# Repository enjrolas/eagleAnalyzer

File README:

Eagle Analyzer is a tool I built to learn more about what electronic
components hackers use in open-source electronic circuits.  There are
a couple files here.  Boards.py scrapes github for all .brd and
associated .sch files (.brd is the file format for circuit layout in
the popular circuit design software EagleCAD).  It's a little hacky (I
hardcoded how many pages are in the github search results), but it
pulls down all the eagle files.  

It's tricky to know if a file is an eagle file without looking inside
it.  .sch files are quite common in code, so just downloading all the
.sch files on github will give a lot of noise.  .brd files are less
common -- apart from eagle, it seems like the naming convention is
only used for some android code, and not very frequently.  To learn
the names of the components, though, we need the .sch files.  So, I
search for .brd files, download those files, and then check to see if
there's a .sch file with the same filepath.  If so, it's a good bet
that these are eagle files.

The next thing to do is to make a histogram to count the
frequency each component is used.  Histogram.py does exactly this.
Building the histogram itself is a bit tricky, because
people will give different names to the same components.  For example,
some people call a resistor 'R' and others call it 'RESISTOR'  -- it
depends on what library they use and whatever the naming convention
is.  So, some of this will require smart intervention, but to get
started, I use the ever-delightful beautifulSoup library to go through the .sch files and look for the <parts> tag,
Inside that tag are a bunch of <part> tags, each one listing the
unique parts in the circuit.  Each part has a 'deviceset' parameter
that's the closest thing to a unique name for a part that we're gonna
get, so I pull that parameter as the part name.  For each name, I
check a list of existing names that I've pulled to see if I've already
seen this name before.  If so, I add one to the number of times I've
seen this device.  If not, I add the device name to the list.

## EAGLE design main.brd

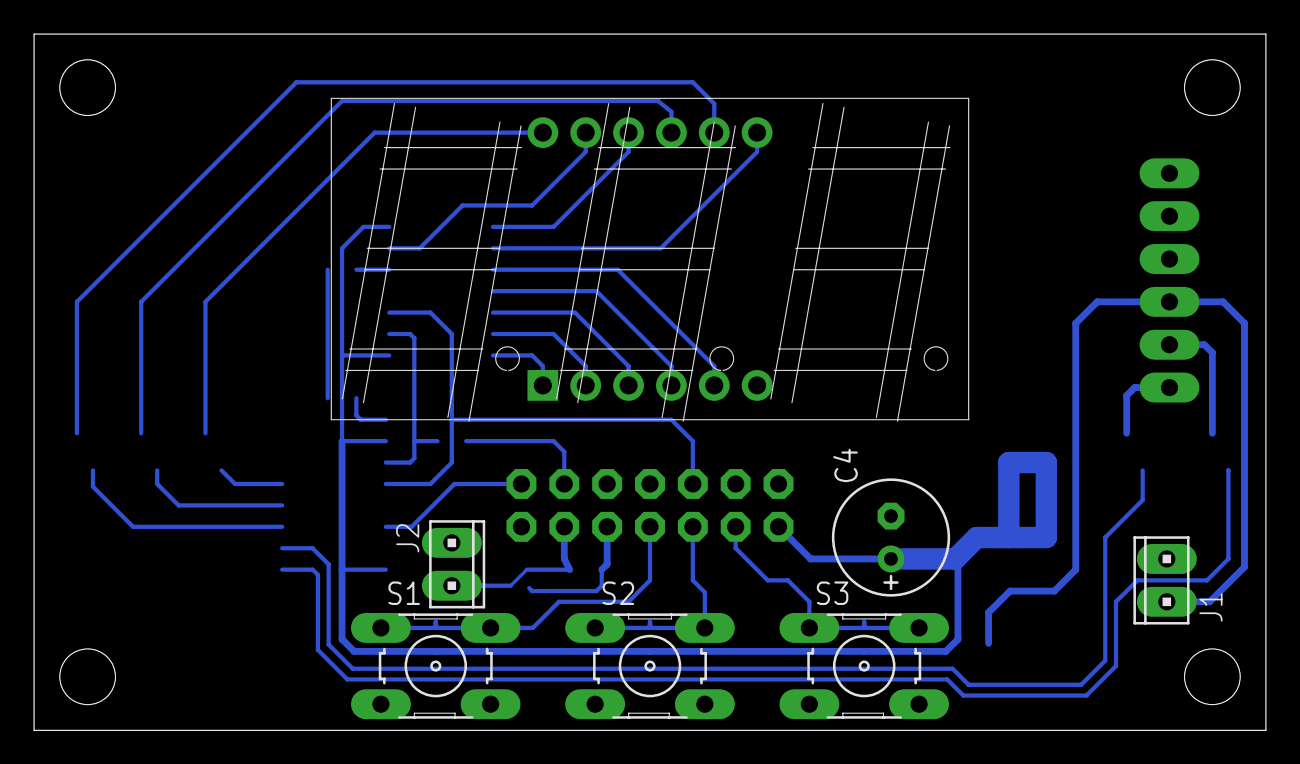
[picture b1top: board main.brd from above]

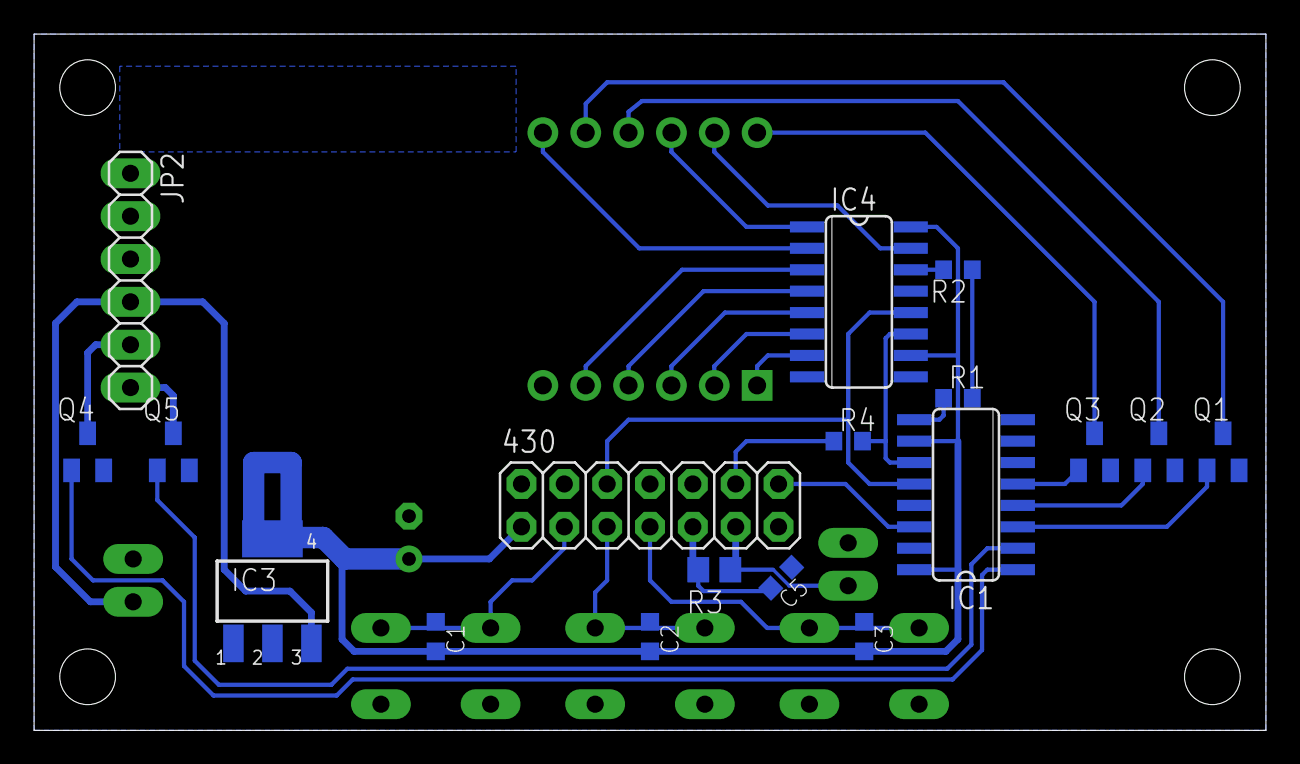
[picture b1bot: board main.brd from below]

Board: 2 copper layers, 73.0 x 41.3 mm, 25 parts (18 on the bottom side), 33 nets.

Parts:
430: 2X07
C1, C2, C3: C0603K
C4: E2,5-7
C5: 470nF; C0603K
IC1, IC4: 74LS595D; SO16
IC3: 317EMP; SOT223
J1, J2: 10X02MTA
JP2: 1X06
Q1, Q2, Q3, Q4, Q5: BSS123; SOT23
R1, R2, R4: 0; R0603
R3: 720ish; R0805
S1, S2, S3: B3F-10XX
U$1: BL-T52C-31; BL-T52X-31

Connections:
+5V: IC3.3, J1.2, JP2.4
GND: 430.2, 430.13, C4.-, C5.1, IC1.8, IC1.13, IC3.1, IC4.8, IC4.13, J1.1, J2.2, JP2.2, JP2.3, Q1.2, Q2.2, Q3.2, Q4.2, Q5.2, S1.3, S1.4, S2.3, S2.4, S3.3, S3.4
unnamed: IC4.15, U$1.P$8
unnamed: IC4.1, U$1.P$9
unnamed: IC4.7, U$1.P$1
unnamed: IC4.6, U$1.P$2
unnamed: IC4.5, U$1.P$3
unnamed: IC4.4, U$1.P$4
unnamed: IC4.3, U$1.P$5
unnamed: IC4.2, U$1.P$12
unnamed: Q1.3, U$1.P$11
unnamed: Q2.3, U$1.P$10
unnamed: Q3.3, U$1.P$7
unnamed: IC1.3, Q1.1
unnamed: 430.14, IC1.14
unnamed: IC4.14, R2.2
unnamed: 430.7, C3.1, S1.1, S1.2
unnamed: IC1.9, R1.1
unnamed: 430.11, J2.1, JP2.1, R3.1
unnamed: 430.3, C1.1, S3.1, S3.2
unnamed: R1.2, R2.1
unnamed: IC1.1, Q4.1
unnamed: IC1.11, IC4.11, R4.2
unnamed: IC1.4, Q2.1
unnamed: JP2.5, Q4.3
unnamed: IC1.5, Q3.1
unnamed: IC1.2, Q5.1
unnamed: 430.12, R4.1
unnamed: JP2.6, Q5.3
unnamed: 430.5, C2.1, S2.1, S2.2
unnamed: 430.6, IC1.12, IC4.12
unnamed: 430.9, C5.2, R3.2
VCC: 430.1, C1.2, C2.2, C3.2, C4.+, IC1.10, IC1.16, IC3.4, IC4.10, IC4.16

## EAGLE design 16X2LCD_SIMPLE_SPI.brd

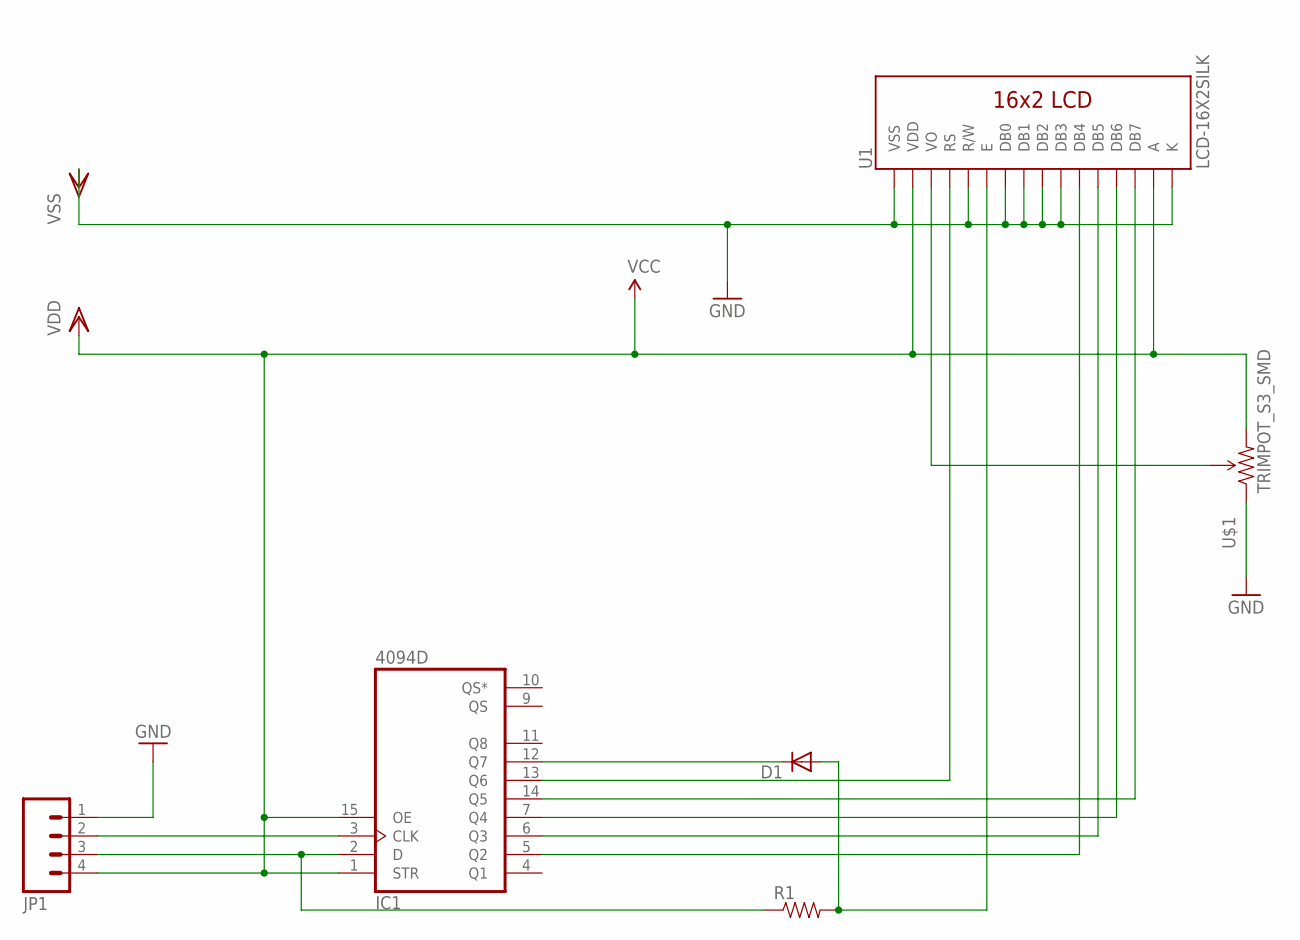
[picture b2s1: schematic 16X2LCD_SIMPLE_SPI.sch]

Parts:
D1: DIODESMA; SMA-DIODE
IC1: 4094D; SO16
JP1: M04PTH; 1X04
R1: RESISTOR1206; 1206
U1: LCD-16X2SILK; LCD-16X2
U$1: TRIMPOT_S3_SMD

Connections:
CLK: IC1.3 (CLK), JP1.2
DATA: IC1.2 (D), JP1.3, R1.1
GND: IC1.8 (VSS), JP1.1, U1.1 (VSS), U1.5 (R/W), U1.7 (DB0), U1.8 (DB1), U1.9 (DB2), U1.10 (DB3), U1.16 (K), U$1.P$1 (CCW)
unnamed: IC1.13 (Q6), U1.4 (RS)
unnamed: D1.A, R1.2, U1.6 (E)
unnamed: U1.3 (VO), U$1.P$2 (WIPER)
unnamed: D1.C, IC1.12 (Q7)
unnamed: IC1.5 (Q2), U1.11 (DB4)
unnamed: IC1.6 (Q3), U1.12 (DB5)
unnamed: IC1.7 (Q4), U1.13 (DB6)
unnamed: IC1.14 (Q5), U1.14 (DB7)
VDD: IC1.1 (STR), IC1.15 (OE), IC1.16 (VDD), JP1.4, U1.2 (VDD), U1.15 (A), U$1.P$3 (CW)

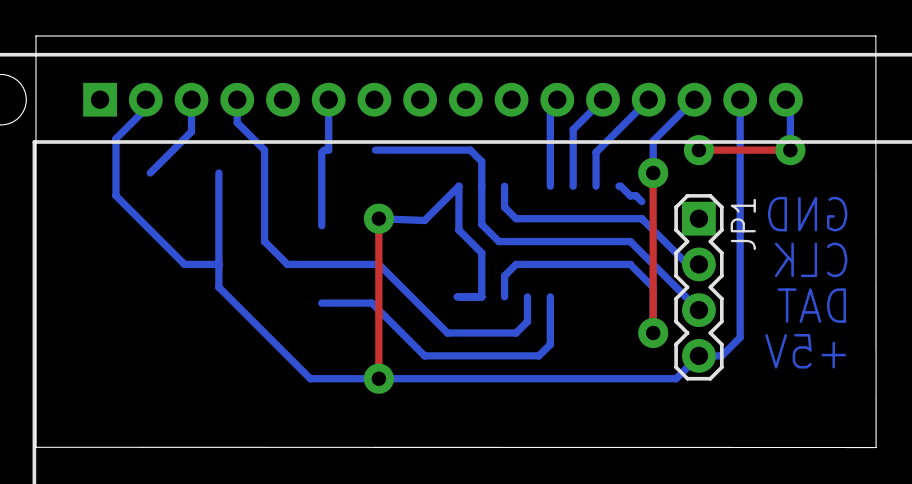
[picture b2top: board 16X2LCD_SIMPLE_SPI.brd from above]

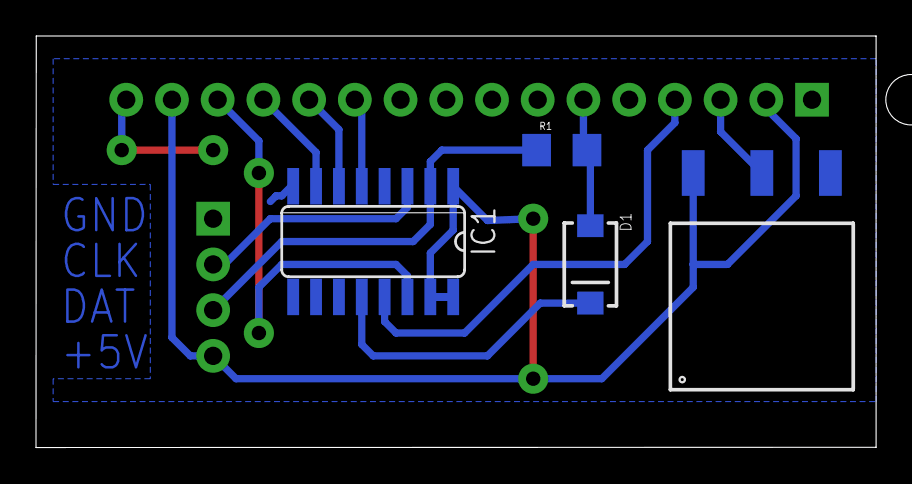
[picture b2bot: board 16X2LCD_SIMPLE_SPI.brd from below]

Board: 2 copper layers, 46.7 x 22.9 mm, 6 parts (4 on the bottom side), 12 nets.

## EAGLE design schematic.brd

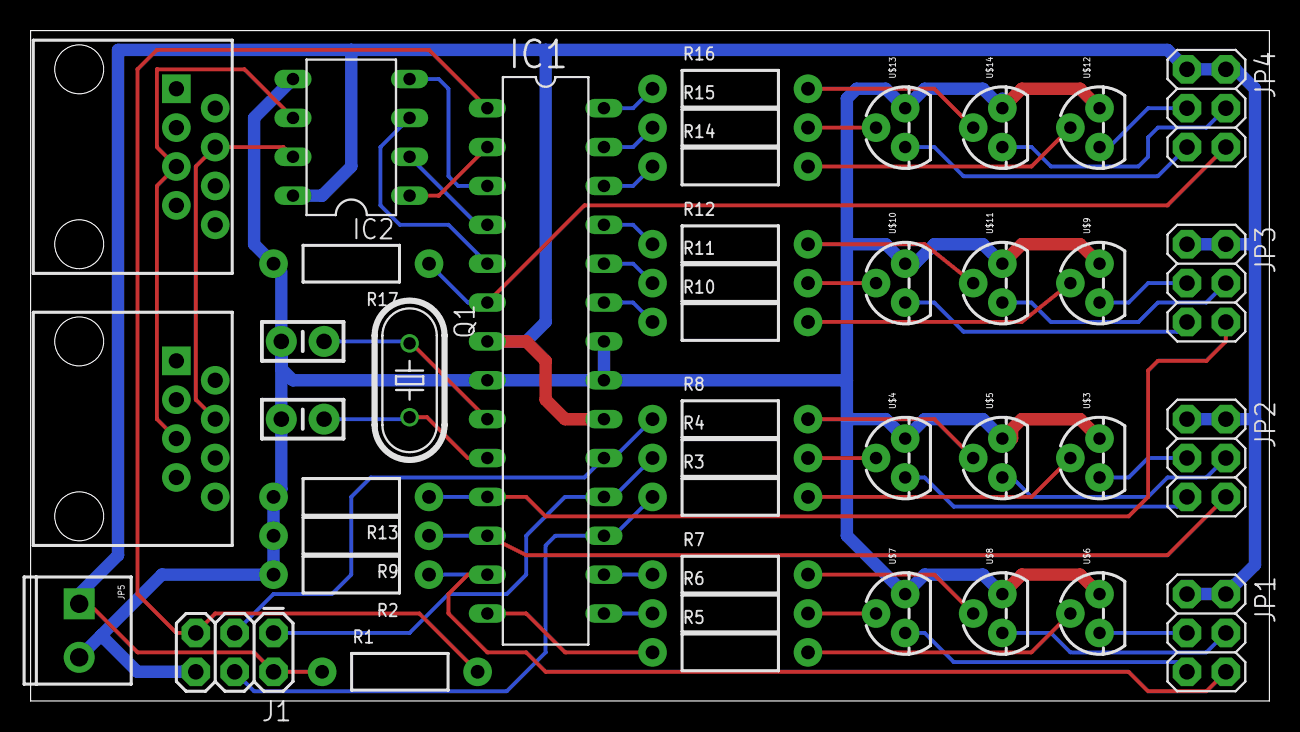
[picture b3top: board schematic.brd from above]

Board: 2 copper layers, 81.0 x 43.8 mm, 42 parts (0 on the bottom side), 51 nets.

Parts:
C1, C2: CAP-PTH-SMALL-KIT
IC1: MEGA8-P; DIL28-3
IC2: MAX481CPA; DIL08
J1: AVR_SPI_PRG_6PTH; 2X3
JP1, JP2, JP3, JP4: 2X03
JP5: SCREWTERMINAL-3.5MM-2
Q1: HC49U-V
R1, R2, R3, R4, R5, R6, R7, R8, R9, R10, R11, R12, R13, R14, R15, R16, R17: AXIAL-0.4
U$1, U$2: RJ45-8PTH; RJ45-8
U$3, U$4, U$5, U$6, U$7, U$8, U$9, U$10, U$11, U$12, U$13, U$14: TRANSISTOR_NPN_2PTH; TO-92

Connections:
GND: C1.2, C2.2, IC1.8, IC1.21, IC1.22, IC2.5, J1.6, JP5.2, R2.P$2, R9.P$2, R13.P$2, R17.P$2, U$3.3, U$4.3, U$5.3, U$6.3, U$7.3, U$8.3, U$9.3, U$10.3, U$11.3, U$12.3, U$13.3, U$14.3
unnamed: IC2.7, U$1.4, U$2.4
unnamed: IC2.6, U$1.5, U$2.5
unnamed: IC1.26, R14.P$1
unnamed: C2.1, IC1.9, Q1.1
unnamed: C1.1, IC1.10, Q1.2
unnamed: JP1.3, U$6.1
unnamed: IC1.2, IC2.1
unnamed: IC1.3, IC2.4
unnamed: JP1.5, U$7.1
unnamed: JP1.4, U$8.1
unnamed: IC1.27, R15.P$1
unnamed: IC1.14, R5.P$1
unnamed: IC1.15, R6.P$1
unnamed: IC1.13, JP1.6, R2.P$1
unnamed: IC1.5, IC2.3
unnamed: R5.P$2, U$6.2
unnamed: IC1.1, J1.5, R1.P$2
unnamed: R6.P$2, U$7.2
unnamed: R7.P$2, U$8.2
unnamed: IC1.12, JP2.6, R9.P$1
unnamed: IC1.4, IC2.2
unnamed: R3.P$2, U$3.2
unnamed: R4.P$2, U$4.2
unnamed: R8.P$2, U$5.2
unnamed: IC1.19, J1.3, R8.P$1
unnamed: IC1.16, R7.P$1
unnamed: JP2.3, U$3.1
unnamed: JP2.5, U$4.1
unnamed: JP2.4, U$5.1
unnamed: IC1.11, JP3.6, R13.P$1
unnamed: R10.P$2, U$9.2
unnamed: R11.P$2, U$10.2
unnamed: R12.P$2, U$11.2
unnamed: IC1.24, R11.P$1
unnamed: IC1.25, R12.P$1
unnamed: JP3.3, U$9.1
unnamed: JP3.5, U$10.1
unnamed: JP3.4, U$11.1
unnamed: IC1.6, JP4.6, R17.P$1
unnamed: R14.P$2, U$12.2
unnamed: R15.P$2, U$13.2
unnamed: R16.P$2, U$14.2
unnamed: IC1.23, R10.P$1
unnamed: IC1.28, R16.P$1
unnamed: JP4.3, U$12.1
unnamed: JP4.5, U$13.1
unnamed: JP4.4, U$14.1
unnamed: IC1.17, J1.4, R3.P$1
unnamed: IC1.18, J1.1, R4.P$1
VCC: IC1.7, IC1.20, IC2.8, J1.2, JP1.1, JP1.2, JP2.1, JP2.2, JP3.1, JP3.2, JP4.1, JP4.2, JP5.1, R1.P$1

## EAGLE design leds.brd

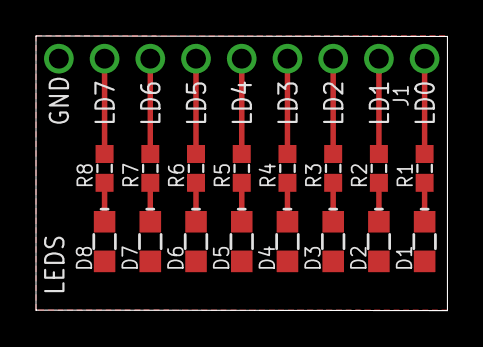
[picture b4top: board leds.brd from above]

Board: 2 copper layers, 22.9 x 15.3 mm, 17 parts (0 on the bottom side), 17 nets.

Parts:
D1, D2, D3, D4, D5, D6, D7, D8: D0805
J1: PHSP254P2286X254X1154-9S
R1, R2, R3, R4, R5, R6, R7, R8: 390; RESC0603

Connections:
GND: D1.2, D2.2, D3.2, D4.2, D5.2, D6.2, D7.2, D8.2, J1.9
unnamed: D1.1, R1.P$1
unnamed: D2.1, R2.P$1
unnamed: D3.1, R3.P$1
unnamed: D4.1, R4.P$1
unnamed: D5.1, R5.P$1
unnamed: D6.1, R6.P$1
unnamed: D7.1, R7.P$1
unnamed: D8.1, R8.P$1
unnamed: J1.8, R8.P$2
unnamed: J1.7, R7.P$2
unnamed: J1.6, R6.P$2
unnamed: J1.5, R5.P$2
unnamed: J1.4, R4.P$2
unnamed: J1.3, R3.P$2
unnamed: J1.2, R2.P$2
unnamed: J1.1, R1.P$2

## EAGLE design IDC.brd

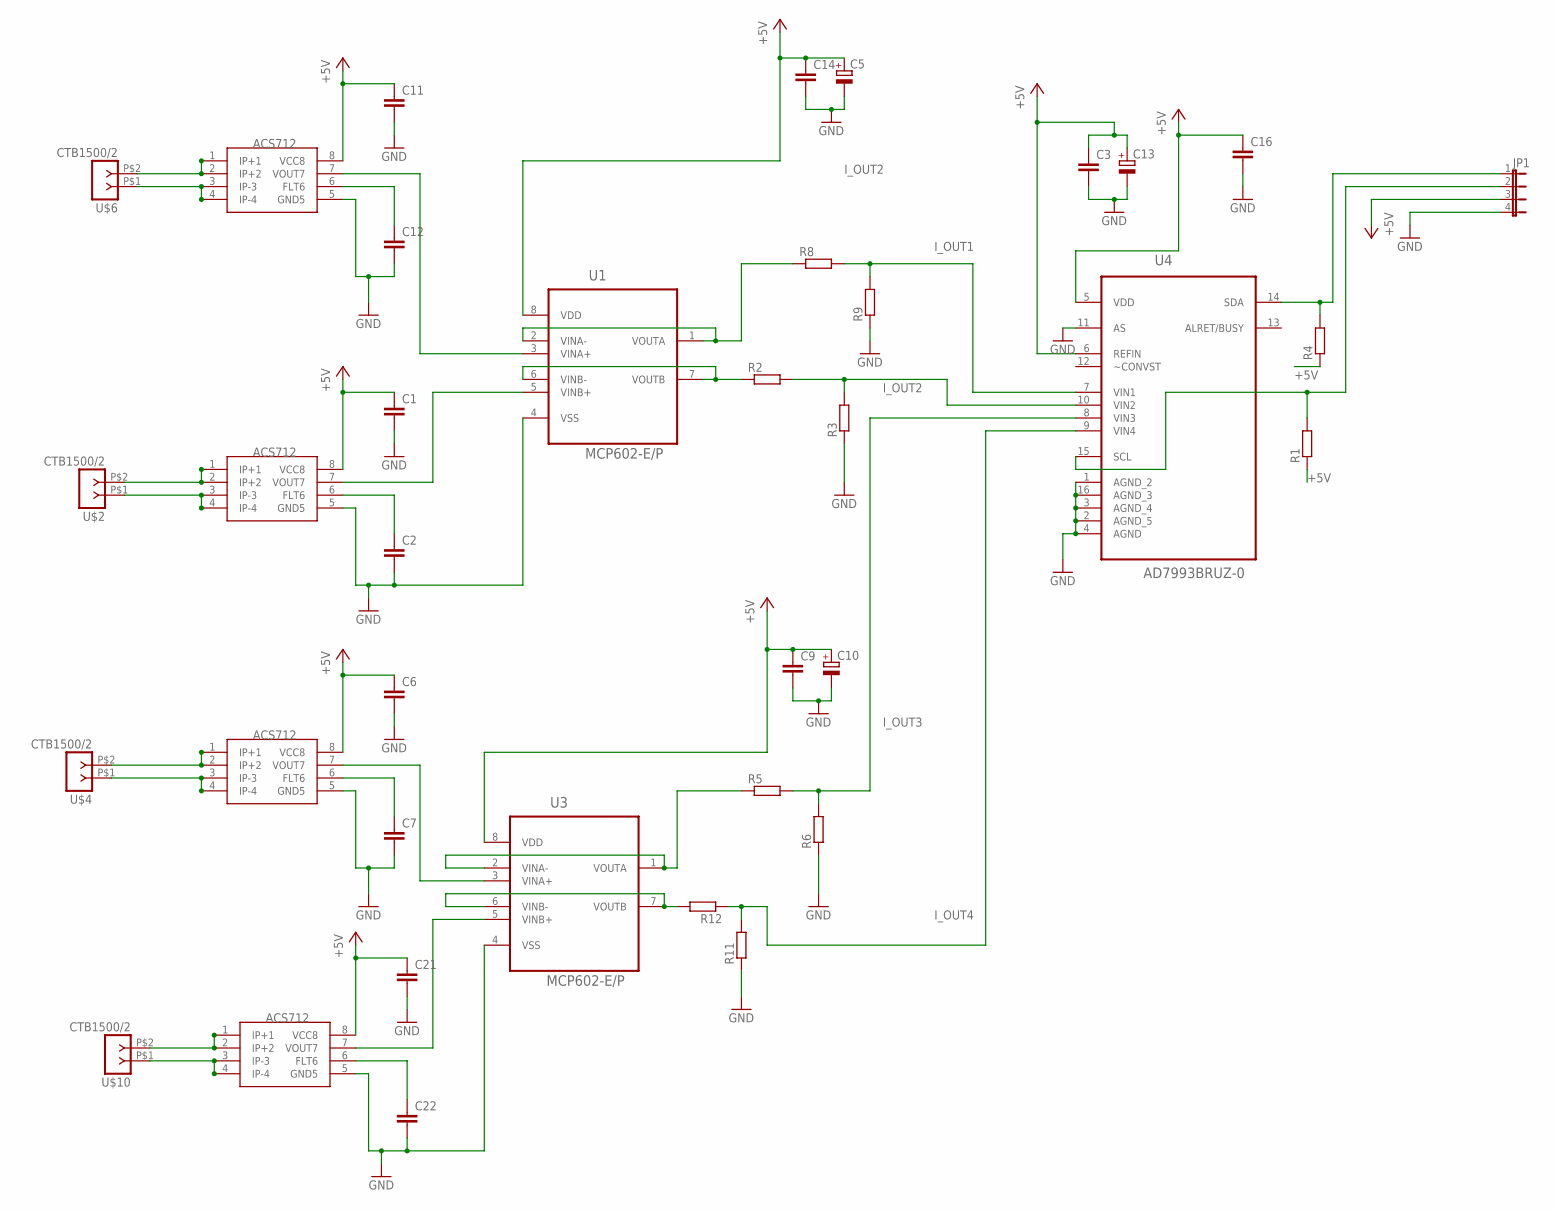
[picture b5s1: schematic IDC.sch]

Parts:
C1, C2, C3, C6, C7, C9, C11, C12, C14, C21, C22: C-EU025-024X044; C025-024X044
C5, C10, C13: CPOL-EUE2-4; E2-4
C16: C-EU025-025X050; C025-025X050
JP1: JP4E; JP4
R1, R2, R3, R4, R5, R6, R8, R9, R11, R12: R-EU_0207/7; 0207/7
U1, U3: MCP602-E/P; DIP254P762X508-8P
U4: AD7993BRUZ-0; SOP65P640X120-16N
U$1, U$3, U$5, U$9: ACS712; SO8
U$2, U$4, U$6, U$10: CTB1500/2; CTB1500-2

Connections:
+5V: C1.1, C3.1, C5.+, C6.1, C9.1, C10.+, C11.1, C13.+, C14.1, C16.1, C21.1, JP1.3, R1.1, R4.1, U1.8 (VDD), U3.8 (VDD), U4.5 (VDD), U4.6 (REFIN), U$1.8 (VCC8), U$3.8 (VCC8), U$5.8 (VCC8), U$9.8 (VCC8)
GND: C1.2, C2.2, C3.2, C5.-, C6.2, C7.2, C9.2, C10.-, C11.2, C12.2, C13.-, C14.2, C16.2, C21.2, C22.2, JP1.4, R3.1, R6.1, R9.1, R11.1, U1.4 (VSS), U3.4 (VSS), U4.1 (AGND_2), U4.2 (AGND_5), U4.3 (AGND_4), U4.4 (AGND), U4.11 (AS), U4.16 (AGND_3), U$1.5 (GND5), U$3.5 (GND5), U$5.5 (GND5), U$9.5 (GND5)
I_OUT: R2.1, U1.6 (VINB-), U1.7 (VOUTB)
I_OUT1: R8.2, R9.2, U4.7 (VIN1)
I_OUT2: R2.2, R3.2, R8.1, U1.1 (VOUTA), U1.2 (VINA-), U4.10 (VIN2)
I_OUT3: R5.2, R6.2, U4.8 (VIN3)
I_OUT4: R11.2, R12.1, U4.9 (VIN4)
unnamed: JP1.1, R4.2, U4.14 (SDA)
unnamed: U$1.3 (IP-3), U$1.4 (IP-4), U$2.P$1 (1)
unnamed: JP1.2, R1.2, U4.15 (SCL)
unnamed: C2.1, U$1.6 (FLT6)
unnamed: U$3.3 (IP-3), U$3.4 (IP-4), U$4.P$1 (1)
unnamed: U3.5 (VINB+), U$9.7 (VOUT7)
unnamed: C7.1, U$3.6 (FLT6)
unnamed: U1.5 (VINB+), U$1.7 (VOUT7)
unnamed: R5.1, U3.1 (VOUTA), U3.2 (VINA-)
unnamed: U3.3 (VINA+), U$3.7 (VOUT7)
unnamed: U$5.3 (IP-3), U$5.4 (IP-4), U$6.P$1 (1)
unnamed: C12.1, U$5.6 (FLT6)
unnamed: U$5.1 (IP+1), U$5.2 (IP+2), U$6.P$2 (2)
unnamed: U$1.1 (IP+1), U$1.2 (IP+2), U$2.P$2 (2)
unnamed: U1.3 (VINA+), U$5.7 (VOUT7)
unnamed: U$3.1 (IP+1), U$3.2 (IP+2), U$4.P$2 (2)
unnamed: U$9.1 (IP+1), U$9.2 (IP+2), U$10.P$2 (2)
unnamed: R12.2, U3.6 (VINB-), U3.7 (VOUTB)
unnamed: U$9.3 (IP-3), U$9.4 (IP-4), U$10.P$1 (1)
unnamed: C22.1, U$9.6 (FLT6)

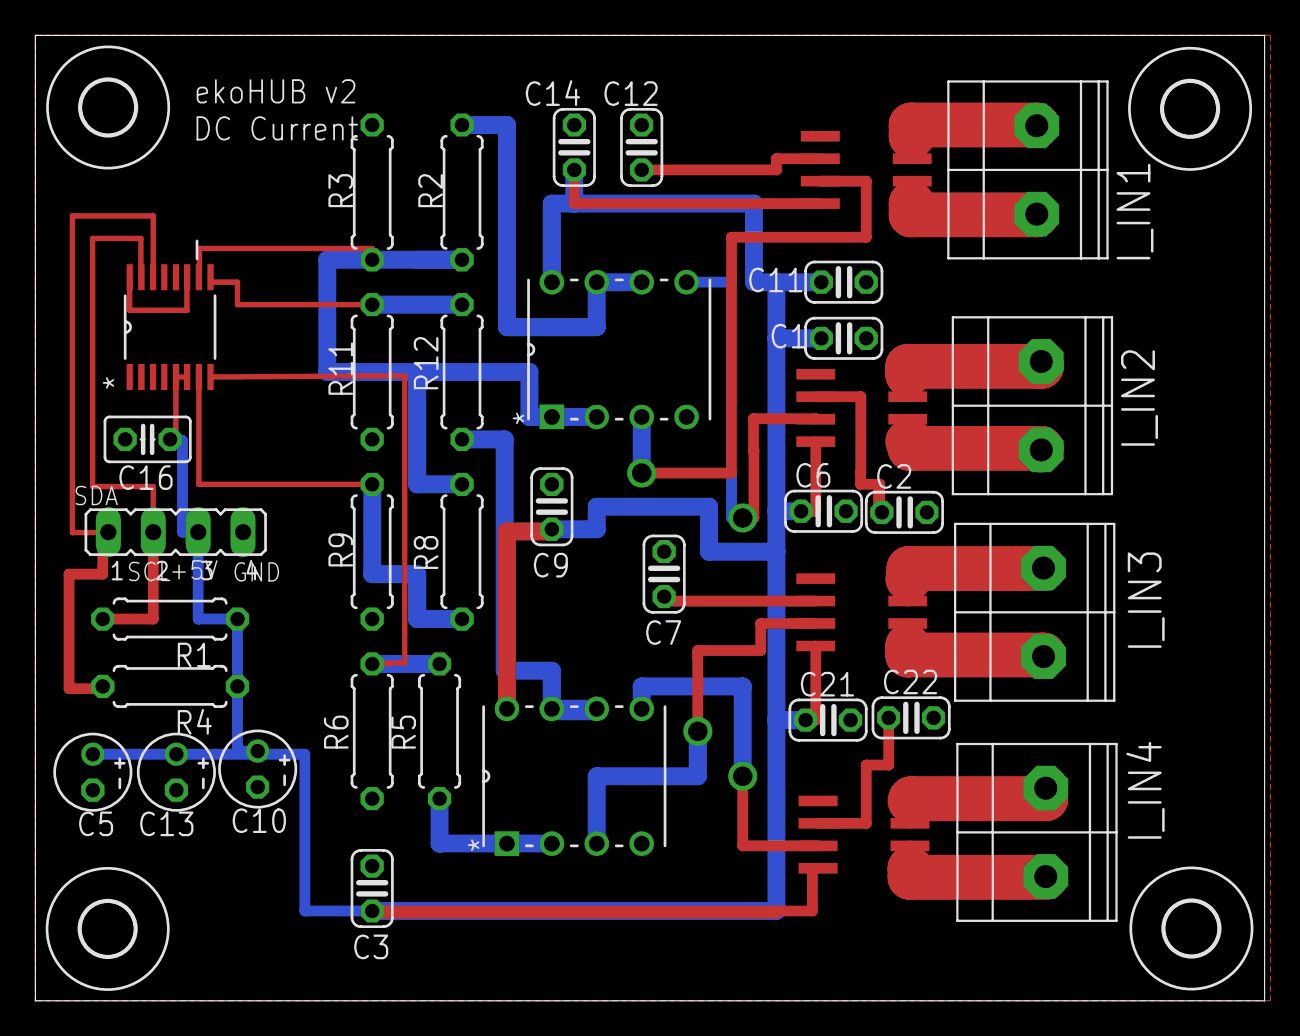
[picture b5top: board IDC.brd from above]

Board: 2 copper layers, 69.5 x 54.6 mm, 41 parts (0 on the bottom side), 27 nets.

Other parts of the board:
U$7, U$8, U$11, U$12: 3,0

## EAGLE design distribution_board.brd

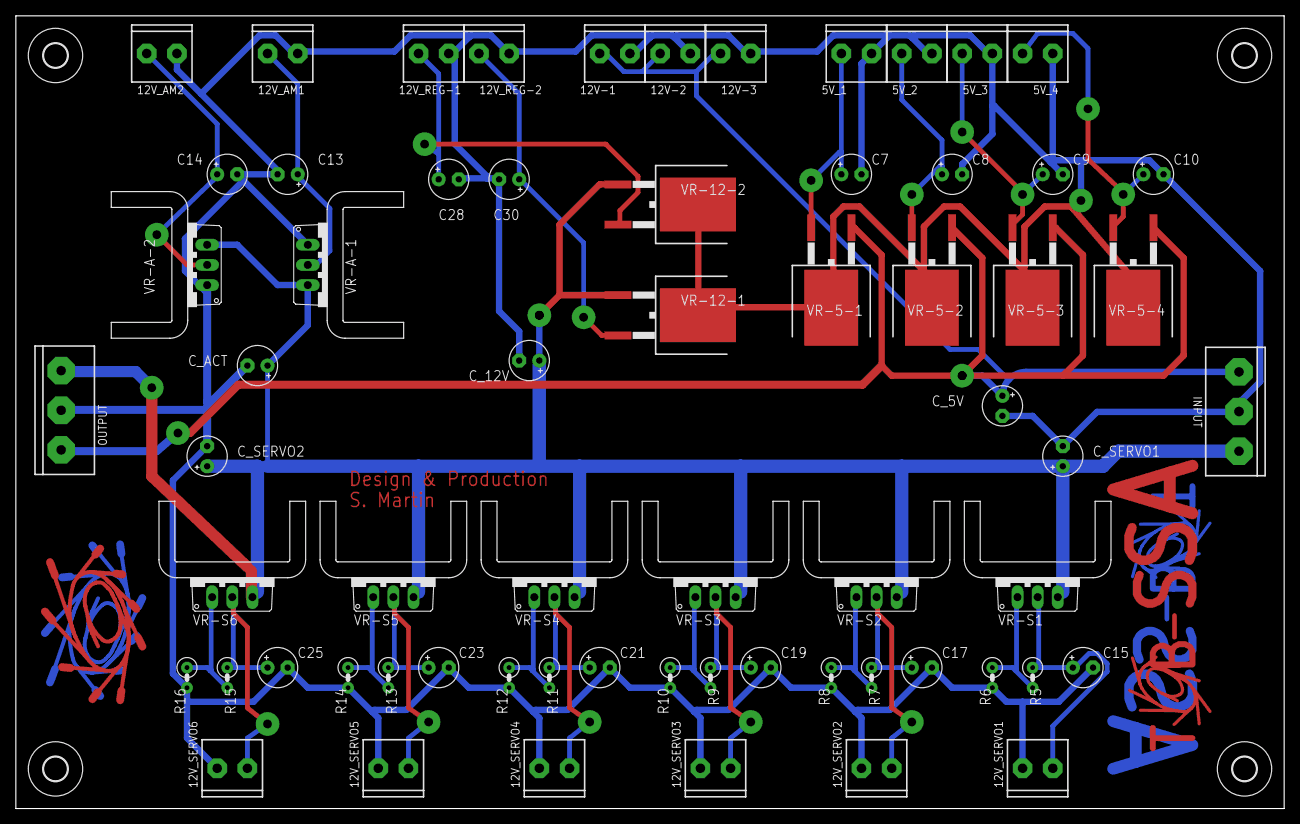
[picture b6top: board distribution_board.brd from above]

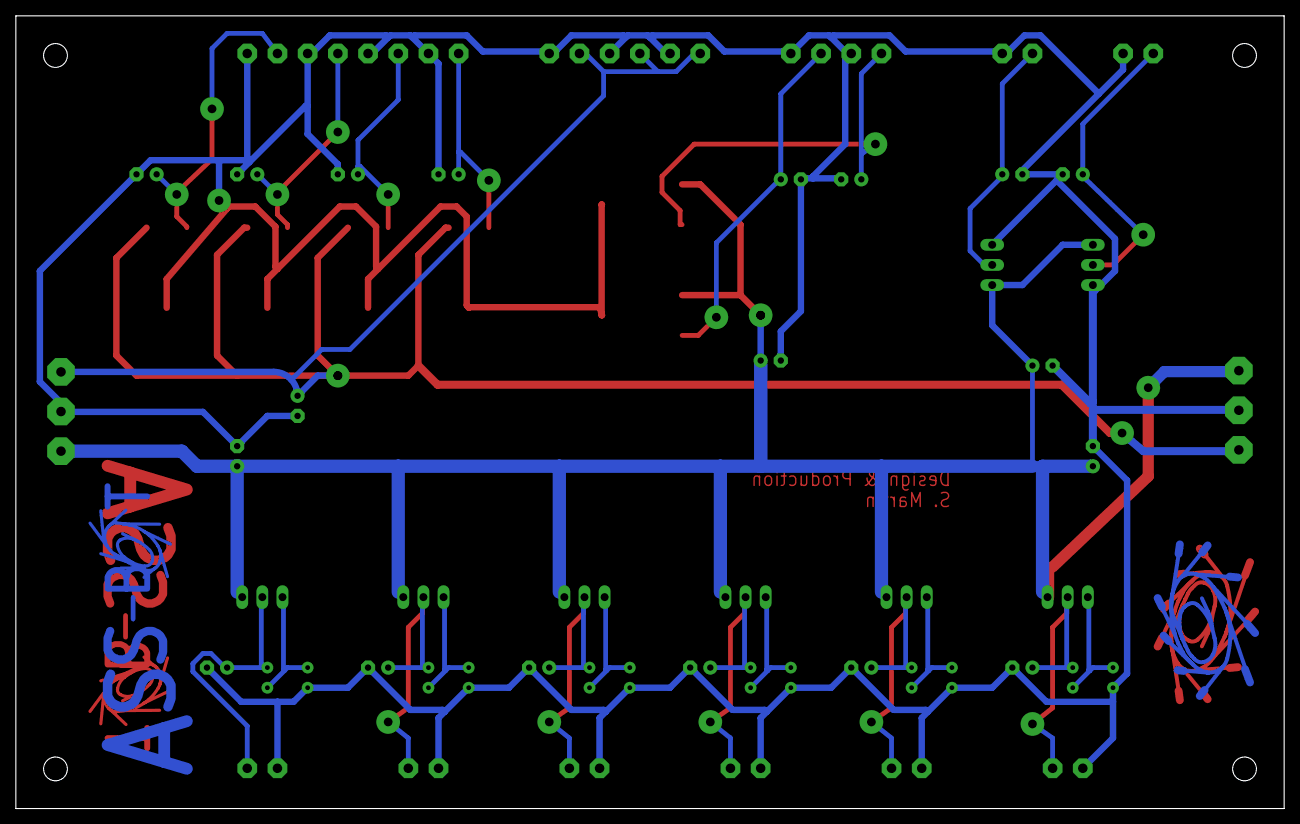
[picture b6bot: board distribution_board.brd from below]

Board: 2 copper layers, 160.0 x 100.0 mm, 73 parts (2 on the bottom side), 23 nets.

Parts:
5V_1, 5V_2, 5V_3, 5V_4, 12V-1, 12V-2, 12V-3, 12V_AM1, 12V_AM2, 12V_REG-1, 12V_REG-2, 12V_SERVO1, 12V_SERVO2, 12V_SERVO3, 12V_SERVO4, 12V_SERVO5, 12V_SERVO6: SC3.81MM; SCREWTERMINAL-3.81MM
C7, C8, C9, C10, C13, C14, C15, C17, C19, C21, C23, C25, C28, C30: 0.1uF; E2,5-5
C_5V, C_12V: 0.33uF; E2,5-5
C_ACT: 0.33uF; E2,5-5
C_SERVO1, C_SERVO2: 0.33uF; E2,5-5
INPUT: SC3.8MM; SCREWTERMINAL-5MM-3
OUTPUT: SC3.8MM; SCREWTERMINAL-5MM-3
R5, R7, R9, R11, R13, R15: 270R; 0207/2V
R6, R8, R10, R12, R14, R16: 1K; 0207/2V
U$1, U$3: LOGO-ASSBOT
U$2, U$4: LOGO-SYNCHROTRON
U$5: LOGO-ASSBOT-SILK
U$6, U$7, U$8, U$9: 3,0
VR-5-1, VR-5-2, VR-5-3, VR-5-4: L7805; TO263
VR-12-1, VR-12-2: L7812; TO263
VR-A-1, VR-A-2: LM1085-12V; TO220V-HEATSINK
VR-S1, VR-S2, VR-S3, VR-S4, VR-S5, VR-S6: LM338T-SINK; TO220V-HEATSINK

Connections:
12V: 12V-1.2, 12V-2.2, 12V-3.2, C_5V.+, INPUT.3, OUTPUT.3, VR-5-1.1, VR-5-2.1, VR-5-3.1, VR-5-4.1
24V: C_12V.+, C_ACT.+, C_SERVO1.+, C_SERVO2.+, INPUT.1, OUTPUT.1, VR-12-1.1, VR-12-2.1, VR-A-1.3, VR-A-2.3, VR-S1.3, VR-S2.3, VR-S3.3, VR-S4.3, VR-S5.3, VR-S6.3
GND: 5V_1.1, 5V_2.1, 5V_3.1, 5V_4.1, 12V-1.1, 12V-2.1, 12V-3.1, 12V_AM1.1, 12V_AM2.1, 12V_REG-1.1, 12V_REG-2.1, 12V_SERVO1.1, 12V_SERVO2.1, 12V_SERVO3.1, 12V_SERVO4.1, 12V_SERVO5.1, 12V_SERVO6.1, C7.-, C8.-, C9.-, C10.-, C13.-, C14.-, C15.-, C17.-, C19.-, C21.-, C23.-, C25.-, C28.-, C30.-, C_5V.-, C_12V.-, C_ACT.-, C_SERVO1.-, C_SERVO2.-, INPUT.2, OUTPUT.2, R6.2, R8.2, R10.2, R12.2, R14.2, R16.2, VR-5-1.3, VR-5-2.3, VR-5-3.3, VR-5-4.3, VR-12-1.3, VR-12-2.3, VR-A-1.1, VR-A-2.1
unnamed: 12V_REG-1.2, C28.+, VR-12-2.2
unnamed: 5V_1.2, C7.+, VR-5-1.2
unnamed: 5V_2.2, C8.+, VR-5-2.2
unnamed: 5V_3.2, C9.+, VR-5-3.2
unnamed: 5V_4.2, C10.+, VR-5-4.2
unnamed: 12V_AM1.2, C13.+, VR-A-1.2
unnamed: 12V_AM2.2, C14.+, VR-A-2.2
unnamed: R5.2, R6.1, VR-S1.1
unnamed: 12V_REG-2.2, C30.+, VR-12-1.2
unnamed: 12V_SERVO1.2, C15.+, R5.1, VR-S1.2
unnamed: 12V_SERVO2.2, C17.+, R7.1, VR-S2.2
unnamed: R7.2, R8.1, VR-S2.1
unnamed: 12V_SERVO3.2, C19.+, R9.1, VR-S3.2
unnamed: R9.2, R10.1, VR-S3.1
unnamed: 12V_SERVO4.2, C21.+, R11.1, VR-S4.2
unnamed: R11.2, R12.1, VR-S4.1
unnamed: 12V_SERVO5.2, C23.+, R13.1, VR-S5.2
unnamed: R13.2, R14.1, VR-S5.1
unnamed: 12V_SERVO6.2, C25.+, R15.1, VR-S6.2
unnamed: R15.2, R16.1, VR-S6.1

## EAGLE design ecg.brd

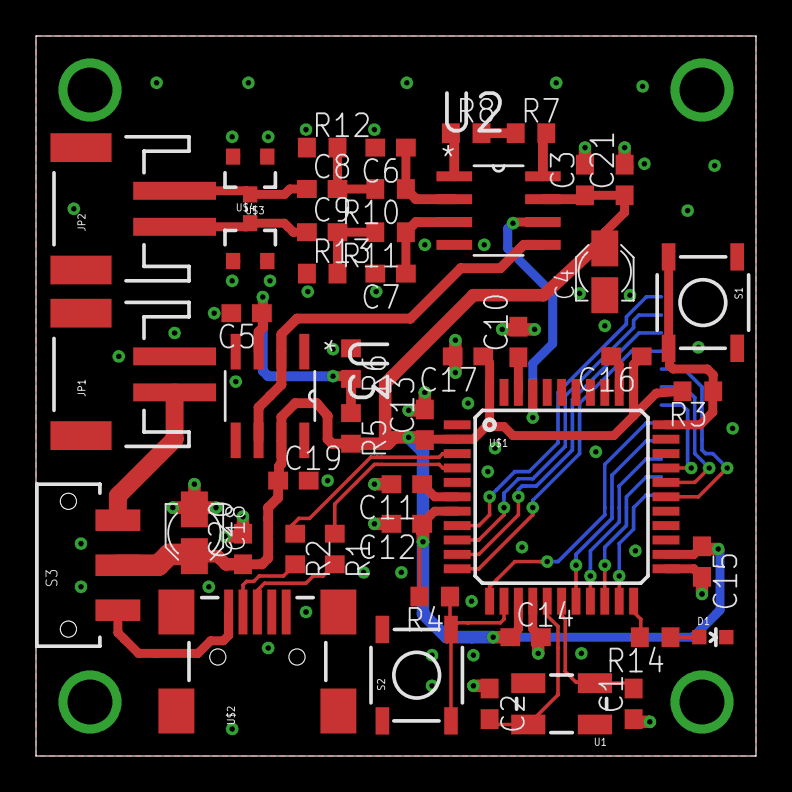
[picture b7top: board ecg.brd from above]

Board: 2 copper layers, 40.0 x 40.0 mm, 48 parts (1 on the bottom side), 40 nets.

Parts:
C1, C2: 18pF; C0603
C3, C5, C10, C11, C12, C13, C14, C15, C16, C17, C19: 0.1uF; C0603
C4, C18: 4.7uF; PANASONIC_A
C6, C7, C8, C9, C20, C21: 1uF; C0603
D1: BLUE; LED-0603
JP1, JP2: M02-JST-2MM-SMT; JST-2-SMD
R1, R2: 22R; R0603
R3, R4: 10k; R0603
R5, R6: 20k; R0603
R7, R8: 82R; R0603
R10, R11: 4.7k; R0603
R12, R13: 1M; R0603
R14: 220; R0603
S1, S2: TACTILE_SWITCH_SMD
S3: SWITCH-SPDT-SMD
U1: 16M; CRYSTAL-SMD-5X3
U2: AD8223ARZ; SOIC127P600X175-8N
U3: OP1177ARZ; SOIC127P600X175-8N
U5: SFW12R-2STE1LF; FCI_SFW12R-2STE1LF
U$1: ATMEGA32U4TQFP; SPARKFUN-DIGITALIC_TQFP44
U$2: USB-MINIB-5PIN; USB-MINIB
U$3, U$4: MMBZ27VCLT1; SOT23-3

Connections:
5V: C3.1, C4.+, C12.1, C13.1, C14.1, C15.1, C16.1, C17.1, C18.+, C19.1, C20.1, C21.1, R3.2, R4.2, R5.2, S3.2, U2.7, U3.7, U$1.2, U$1.7, U$1.14, U$1.24, U$1.34, U$1.44
!HWB: R3.1, S1.3, S1.4, U$1.33
!RESET: R4.1, S2.3, S2.4, U$1.13
+IN: C7.1, R11.1, U2.3
+RG: R7.2, U2.8
-IN: C6.1, R10.1, U2.2
-RG: R8.1, U2.1
ADC: U2.6, U$1.41
CS1: U5.10, U$1.19
CS2: U5.12, U$1.21
D0: U5.1, U$1.8
D1: U5.2, U$1.9
D2: U5.3, U$1.10
D3: U5.4, U$1.11
D4: U5.5, U$1.28
D5: U5.6, U$1.29
D6: U5.7, U$1.30
D7: U5.8, U$1.12
D+: R1.1, U$1.4
D-: R2.1, U$1.3
D/I: U5.9, U$1.18
GND: C1.1, C2.1, C3.2, C4.-, C5.2, C6.2, C7.2, C10.2, C11.2, C12.2, C13.2, C14.2, C15.2, C16.2, C17.2, C18.-, C19.2, C20.2, C21.2, D1.C, JP1.2, R6.1, R12.1, R13.1, S1.1, S1.2, S2.1, S2.2, U2.4, U3.4, U$1.5, U$1.15, U$1.23, U$1.35, U$1.43, U$2.GND, U$3.1, U$3.2, U$4.1, U$4.2
unnamed: R1.2, U$2.D+
unnamed: R2.2, U$2.D-
unnamed: C9.1, JP2.1, U$4.3
unnamed: C8.1, JP2.2, U$3.3
unnamed: C10.1, U$1.42
unnamed: C11.1, U$1.6
unnamed: D1.A, R14.1
unnamed: C8.2, R10.2, R12.2
unnamed: C9.2, R11.2, R13.2
R/W: U5.11, U$1.20
REF: U2.5, U3.2, U3.6
REF_DIV: C5.1, R5.1, R6.2, U3.3
RG/2: R7.1, R8.2
TX: R14.2, U$1.22
VBAT: JP1.1, S3.3
VBUS: S3.1, U$2.VBUS
X1: C1.2, U1.1, U$1.17
X2: C2.2, U1.3, U$1.16

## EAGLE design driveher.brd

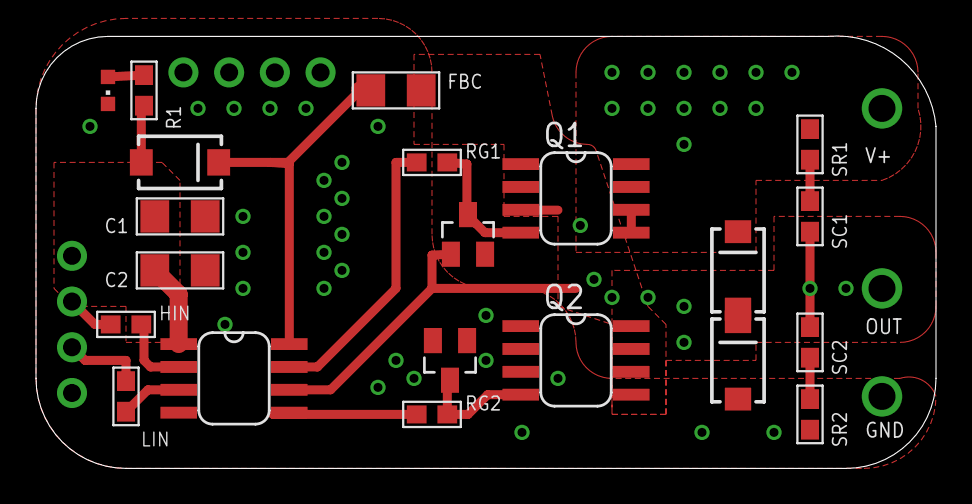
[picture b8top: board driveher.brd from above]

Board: 2 copper layers, 50.0 x 24.0 mm, 23 parts (0 on the bottom side), 16 nets.

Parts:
C1, C2: 1206
D1, D2: SOT23
FBC: 1206
FBD, FBD1, FBD2: SCHOTTKY; SMA-DIODE
HIN: 0603
JP1, JP2: 1X04_ROUND
LED1: CHIPLED_0603
LIN: 0603
Q1, Q2: PSMN; SO-08
R1: 0603
RG1, RG2: 0603
SC1, SC2: 0603
SR1, SR2: 0603
U$1: IRS218-67; SO-08

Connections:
12V: C1.2, C2.2, FBD.A, JP1.4, R1.2, U$1.1
FLOAT: FBC.1, FBD.C, U$1.8
G1: D1.3, Q1.4, RG1.2
G2: D2.3, Q2.4, RG2.2
GND: C1.1, C2.1, D2.1, FBD2.A, JP1.1, JP2.1, JP2.2, JP2.3, JP2.4, LED1.C, Q2.1, Q2.2, Q2.3, SR2.2, U$1.4
HIN-P: HIN.2, U$1.2
HOUT: RG1.1, U$1.7
LIN-P: LIN.2, U$1.3
LOUT: RG2.1, U$1.5
unnamed: LED1.A, R1.1
unnamed: SC1.1, SR1.2
unnamed: HIN.1, JP1.3
unnamed: JP1.2, LIN.1
OUT: D1.1, FBC.2, FBD1.A, FBD2.C, Q1.1, Q1.2, Q1.3, Q2.5, Q2.6, Q2.7, Q2.8, SC1.2, SC2.1, U$1.6
P2: SC2.2, SR2.1
V+: FBD1.C, Q1.5, Q1.6, Q1.7, Q1.8, SR1.1

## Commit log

2013-07-18 Sending everything up
2013-11-17 added schematic downloading capability, downloaded all the board and schematics, and wrote the basic parser to build the histogram in histogram.py
2013-11-18 pulled down all the eagle files on github. histogram.py generates a histogram of the frequency of their usage. You can make all the boards on github with ~1460 unique parts
2013-11-18 put all the downloaded files into directories
2013-11-18 trying to purge deleted files
2013-11-18 updated with new gitignore
2013-11-18 fixed a gitignore so I could add .html files

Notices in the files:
parts and their libraries:
SparkFun: Licensing: CC v3.0 Share-Alike You are welcome to use this library for commercial purposes.
